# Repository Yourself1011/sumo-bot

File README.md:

# Sumo Bot

The code for Li Feng Yin and Daniel Zhang's sumo robot, for TEJ3MI

## Images

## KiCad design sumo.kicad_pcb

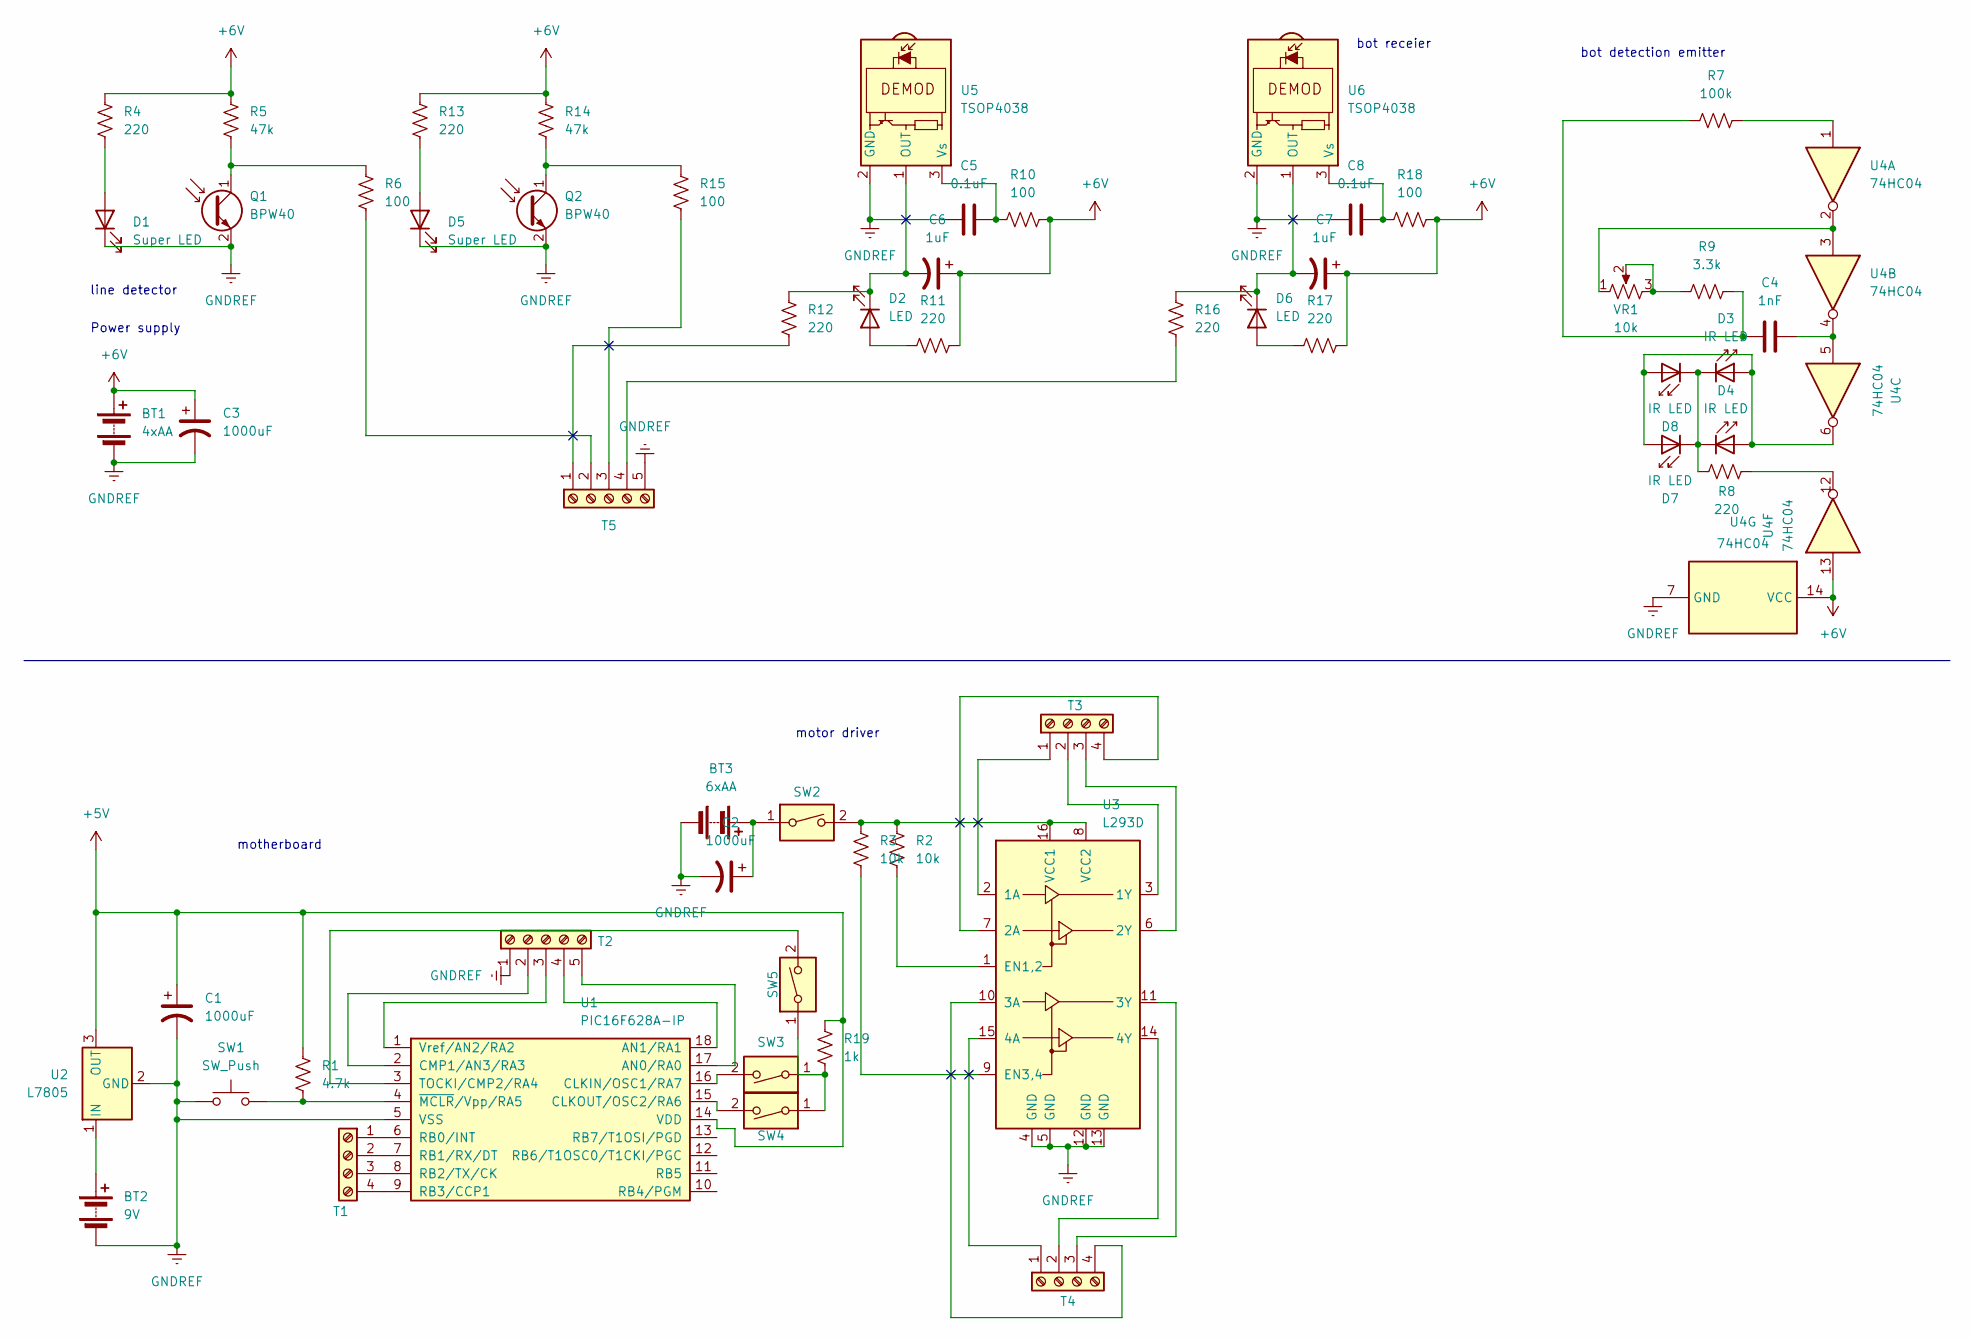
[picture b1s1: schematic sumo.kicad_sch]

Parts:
BT1: 4xAA; Battery_Pads
BT2: 9V; Battery_Pads
BT3: 6xAA; Battery_Pads
C1: 1000uF; C_Radial_D10.0mm_H12.5mm_P5.00mm
C2, C3: 1000uF; C_Radial_D10.0mm_H20.0mm_P5.00mm
C4: 1nF; C_Disc_D7.5mm_W2.5mm_P5.00mm
C5, C8: 0.1uF; C_Disc_D7.5mm_W2.5mm_P5.00mm
C6, C7: 1uF; C_Disc_D7.5mm_W2.5mm_P5.00mm
D1, D5: Super LED; LED_D5.0mm
D2, D6: LED; LED_D5.0mm
D3, D4, D7, D8: IR LED; LED_D5.0mm_IRBlack
Q1, Q2: BPW40; LED_D5.0mm_Clear
R1: 4.7k; R_Axial_DIN0207_L6.3mm_D2.5mm_P7.62mm_Horizontal
R2, R3: 10k; R_Axial_DIN0207_L6.3mm_D2.5mm_P7.62mm_Horizontal
R4, R8, R11, R12, R13, R16, R17: 220; R_Axial_DIN0207_L6.3mm_D2.5mm_P7.62mm_Horizontal
R5, R14: 47k; R_Axial_DIN0207_L6.3mm_D2.5mm_P7.62mm_Horizontal
R6, R10, R15, R18: 100; R_Axial_DIN0207_L6.3mm_D2.5mm_P7.62mm_Horizontal
R7: 100k; R_Axial_DIN0207_L6.3mm_D2.5mm_P7.62mm_Horizontal
R9: 3.3k; R_Axial_DIN0207_L6.3mm_D2.5mm_P7.62mm_Horizontal
R19: 1k; R_Axial_DIN0207_L6.3mm_D2.5mm_P7.62mm_Horizontal
SW1: SW_Push; SW_PUSH_1P1T_6x3.5mm_H5.0_APEM_MJTP1250
SW2, SW3, SW4: SW_DIP_x01; SW_DIP_SPSTx01_Slide_9.78x4.72mm_W7.62mm_P2.54mm
SW5: SW_DIP_x01; SolderWire-0.1sqmm_1x02_P3.6mm_D0.4mm_OD1mm
T1, T3, T4: Screw_Terminal_01x04; TerminalBlock_MetzConnect_Type101_RT01604HBWC_1x04_P5.08mm_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
T2, T5: Screw_Terminal_01x05; TerminalBlock_MetzConnect_Type101_RT01605HBWC_1x05_P5.08mm_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
U1: PIC16F628A-IP; DIP-18_W7.62mm
U2: L7805; TO-220-3_Vertical
U3: L293D; DIP-16_W7.62mm
U4: 74HC04; DIP-14_W7.62mm
U5, U6: TSOP4038; Vishay_MOLD-3Pin
VR1: 10k; Potentiometer_Bourns_3386P_Vertical

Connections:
+5V: C1.1, R1.1, R19.1, U1.14 (VDD), U2.3 (OUT)
+6V: BT1.1 (+), C3.1, C6.1, C7.1, R4.1, R5.1, R10.2, R11.1, R13.1, R14.1, R17.1, R18.2, U4.13, U4.14 (VCC)
GNDREF: BT1.2 (-), BT2.2 (-), BT3.2 (-), C1.2, C2.2, C3.2, C5.1, C8.1, D1.1 (K), D5.1 (K), Q1.2 (E), Q2.2 (E), SW1.1, T2.1, T5.5, U1.5 (VSS), U2.2 (GND), U3.4 (GND), U3.5 (GND), U3.12 (GND), U3.13 (GND), U4.7 (GND), U5.2 (GND), U6.2 (GND)
unnamed: BT2.1 (+), U2.1 (IN)
unnamed: BT3.1 (+), C2.1, SW2.1
unnamed: C4.1, R7.1, R9.2
unnamed: C4.2, U4.4, U4.5
unnamed: D1.2 (A), R4.2
unnamed: D2.2 (A), R11.2
unnamed: C6.2, D2.1 (K), R12.1, U5.1 (OUT)
unnamed: D3.2 (A), D4.2 (A), D7.2 (A), D8.2 (A), U4.6
unnamed: D3.1 (K), D4.1 (K), D7.1 (K), D8.1 (K), R8.1
unnamed: D5.2 (A), R13.2
unnamed: D6.2 (A), R17.2
unnamed: C7.2, D6.1 (K), R16.1, U6.1 (OUT)
unnamed: Q1.1 (C), R5.2, R6.2
unnamed: Q2.1 (C), R14.2, R15.2
unnamed: R7.2, U4.1
unnamed: R8.2, U4.12
unnamed: R9.1, VR1.2, VR1.3
unnamed: R19.2, SW3.1, SW4.1, SW5.1
unnamed: T1.1, U1.6 (RB0/INT)
unnamed: T1.2, U1.7 (RB1/RX/DT)
unnamed: T1.3, U1.8 (RB2/TX/CK)
unnamed: T1.4, U1.9 (RB3/CCP1)
unnamed: T2.2, U1.2 (CMP1/AN3/RA3)
unnamed: T2.3, U1.1 (Vref/AN2/RA2)
unnamed: T2.4, U1.18 (AN1/RA1)
unnamed: T2.5, U1.17 (AN0/RA0)
unnamed: T3.1, U3.2 (1A)
unnamed: T3.2, U3.3 (1Y)
unnamed: T3.3, U3.6 (2Y)
unnamed: T3.4, U3.7 (2A)
unnamed: T4.1, U3.15 (4A)
unnamed: T4.2, U3.14 (4Y)
unnamed: T4.3, U3.11 (3Y)
unnamed: T4.4, U3.10 (3A)
unnamed: R12.2, T5.1
unnamed: R6.1, T5.2
unnamed: R15.1, T5.3
unnamed: R16.2, T5.4
unnamed: SW3.2, U1.16 (CLKIN/OSC1/RA7)
unnamed: SW4.2, U1.15 (CLKOUT/OSC2/RA6)
unnamed: SW5.2, U1.3 (TOCKI/CMP2/RA4)
unnamed: R1.2, SW1.2, U1.4 (~MCLR/Vpp/RA5)
unnamed: R2.1, U3.1 (EN1,2)
unnamed: R3.2, U3.9 (EN3,4)
unnamed: R2.2, R3.1, SW2.2, U3.8 (VCC2), U3.16 (VCC1)
unnamed: U4.2, U4.3, VR1.1
unnamed: C5.2, R10.1, U5.3 (Vs)
unnamed: C8.2, R18.1, U6.3 (Vs)

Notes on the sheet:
motor driver
bot detection emitter
bot receier
motherboard
line detector
Power supply

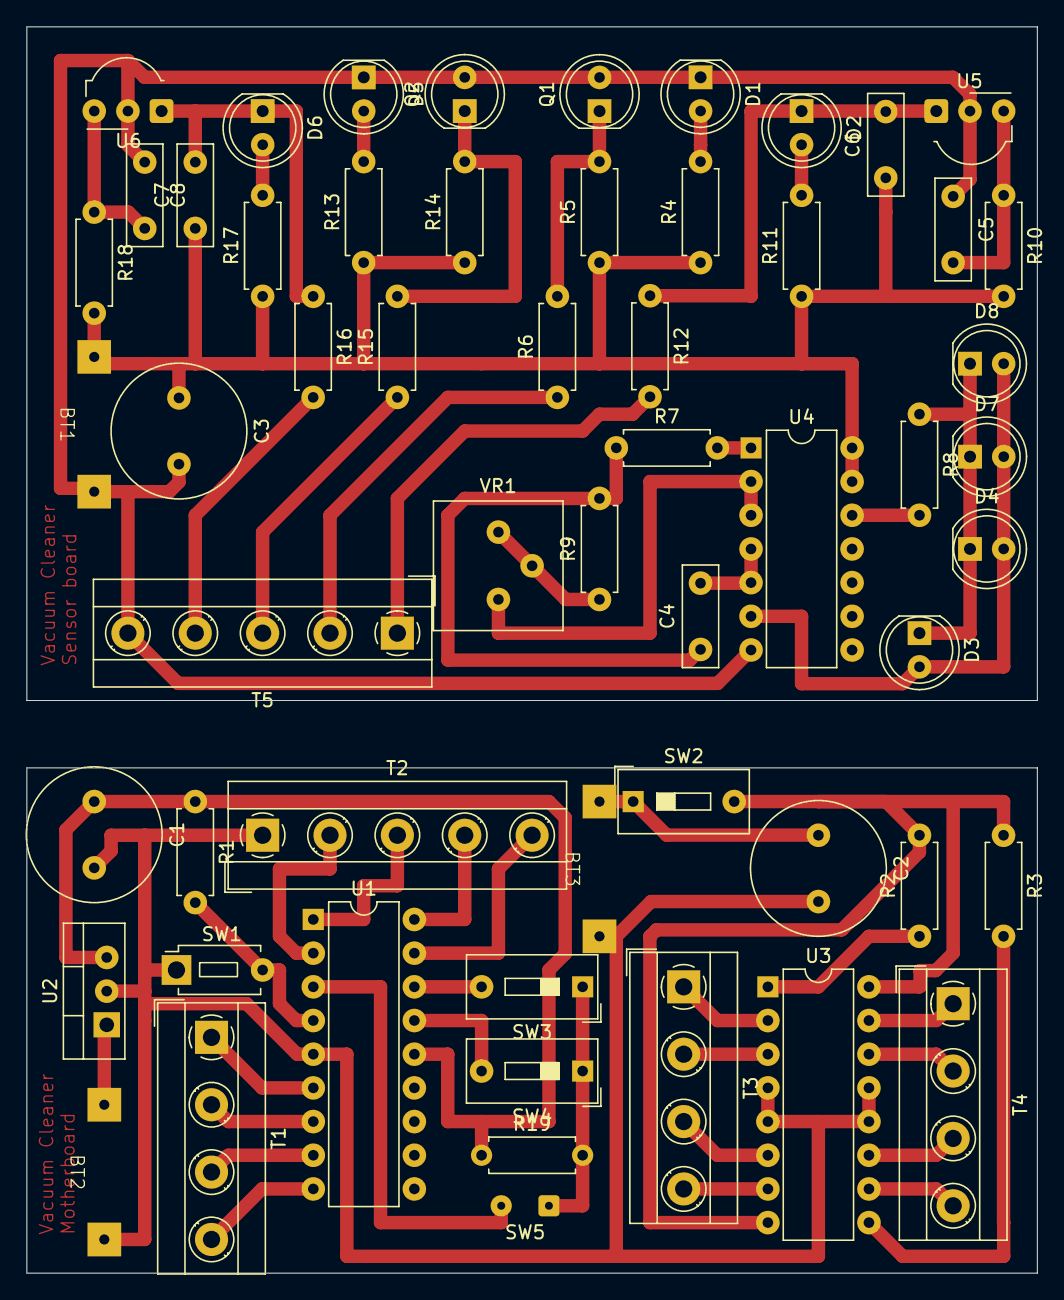
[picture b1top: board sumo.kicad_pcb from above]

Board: 2 copper layers, 76.2 x 94.0 mm, 57 parts (0 on the bottom side), 51 nets.

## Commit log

2024-03-30 Inital commit
2024-03-30 recreate schematic
2024-03-30 component dump
2024-03-30 fix battery footprint
2024-03-30 motherboard
2024-03-30 motor driver
2024-04-02 schematic updates
2024-04-02 connect grounds
2024-04-02 sensors
2024-04-02 ignore backups
2024-04-02 sensor board
2024-04-02 save changes
2024-04-03 finishing touches
2024-04-03 add pull up resistor to switch inputs
2024-04-03 change potentiometer footprint
2024-04-04 ground plane
2024-04-04 change potentiometer pads
2024-04-05 remove ground plane
2024-04-12 some value fixes
2024-04-24 test motor code
2024-05-09 improved code
2024-05-15 reverse bot detection parity
2024-05-15 aiya did not sav
2024-10-27 images attempt
2024-10-27 fix image links
